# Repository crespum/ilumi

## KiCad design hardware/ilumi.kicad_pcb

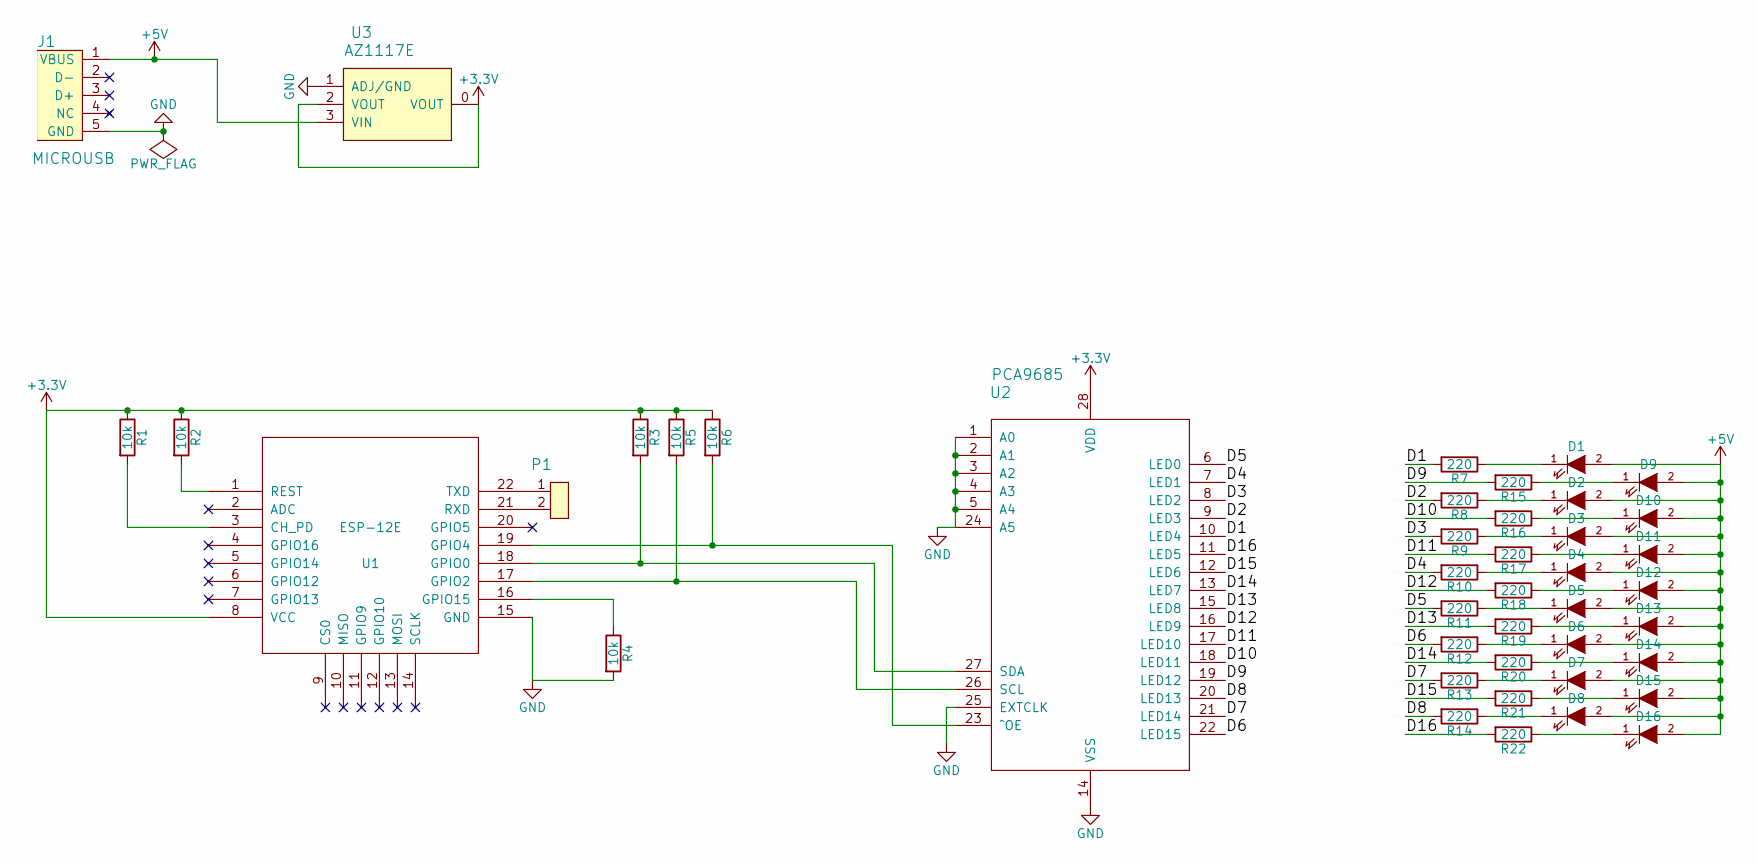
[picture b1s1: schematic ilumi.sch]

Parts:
D1, D2, D3, D4, D5, D6, D7, D8, D9, D10, D11, D12, D13, D14, D15, D16: LED; LED_ILUMI
J1: MICROUSB; MICROUSB_th
P1: 2PIN_MALE; SIP2
R1, R2, R3, R4, R5, R6: 10k; R_0603
R7, R8, R9, R10, R11, R12, R13, R14, R15, R16, R17, R18, R19, R20, R21, R22: 220; R_0603
U1: ESP-12E
U2: PCA9685; HTSSOP28
U3: AZ1117E; SOT223

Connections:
+3V3: R1.1, R2.1, R3.1, R5.1, R6.1, U1.8 (VCC), U2.28 (VDD), U3.0 (VOUT), U3.2 (VOUT)
+5V: D1.2 (A), D2.2 (A), D3.2 (A), D4.2 (A), D5.2 (A), D6.2 (A), D7.2 (A), D8.2 (A), D9.2 (A), D10.2 (A), D11.2 (A), D12.2 (A), D13.2 (A), D14.2 (A), D15.2 (A), D16.2 (A), J1.1 (VBUS), U3.3 (VIN)
/D1: R7.2, U2.10 (LED4)
/D2: R8.2, U2.9 (LED3)
/D3: R9.2, U2.8 (LED2)
/D4: R10.2, U2.7 (LED1)
/D5: R11.2, U2.6 (LED0)
/D6: R12.2, U2.22 (LED15)
/D7: R13.2, U2.21 (LED14)
/D8: R14.2, U2.20 (LED13)
/D9: R15.2, U2.19 (LED12)
/D10: R16.2, U2.18 (LED11)
/D11: R17.2, U2.17 (LED10)
/D12: R18.2, U2.16 (LED9)
/D13: R19.2, U2.15 (LED8)
/D14: R20.2, U2.13 (LED7)
/D15: R21.2, U2.12 (LED6)
/D16: R22.2, U2.11 (LED5)
GND: J1.5 (GND), R4.2, U1.15 (GND), U2.1 (A0), U2.2 (A1), U2.3 (A2), U2.4 (A3), U2.5 (A4), U2.14 (VSS), U2.24 (A5), U2.25 (EXTCLK), U3.1 (ADJ/GND)
unnamed: D1.1 (K), R7.1
unnamed: D2.1 (K), R8.1
unnamed: D3.1 (K), R9.1
unnamed: D4.1 (K), R10.1
unnamed: D5.1 (K), R11.1
unnamed: D6.1 (K), R12.1
unnamed: D7.1 (K), R13.1
unnamed: D8.1 (K), R14.1
unnamed: D9.1 (K), R15.1
unnamed: D10.1 (K), R16.1
unnamed: D11.1 (K), R17.1
unnamed: D12.1 (K), R18.1
unnamed: D13.1 (K), R19.1
unnamed: D14.1 (K), R20.1
unnamed: D15.1 (K), R21.1
unnamed: D16.1 (K), R22.1
unnamed: P1.1, U1.22 (TXD)
unnamed: P1.2, U1.21 (RXD)
unnamed: R1.2, U1.3 (CH_PD)
unnamed: R2.2, U1.1 (REST)
unnamed: R3.2, U1.18 (GPIO0), U2.27 (SDA)
unnamed: R4.1, U1.16 (GPIO15)
unnamed: R5.2, U1.17 (GPIO2), U2.26 (SCL)
unnamed: R6.2, U1.19 (GPIO4), U2.23 (^OE)

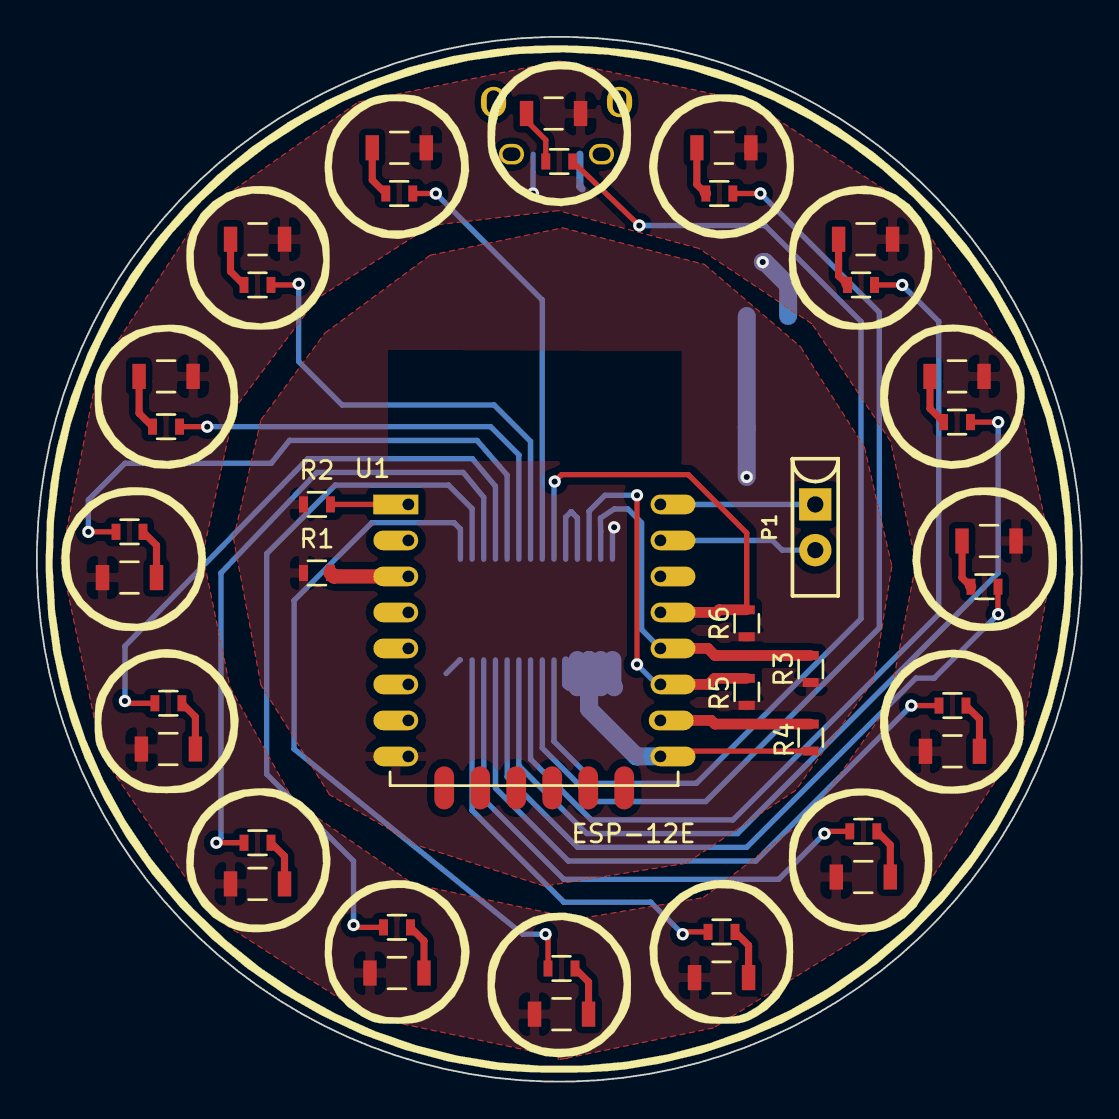
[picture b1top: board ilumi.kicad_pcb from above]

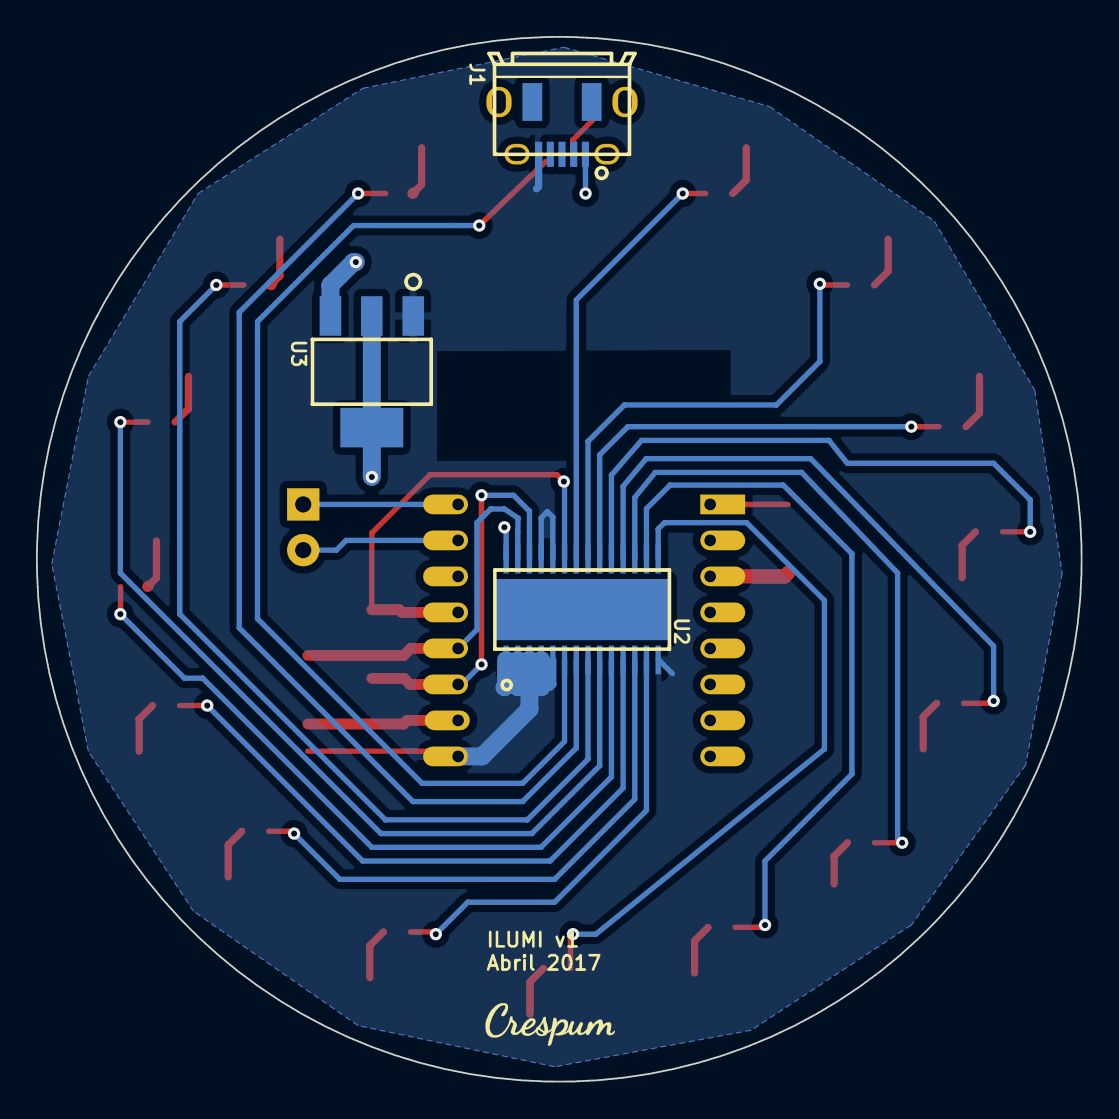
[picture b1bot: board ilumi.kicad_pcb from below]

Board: 2 copper layers, 58.0 x 58.0 mm, 43 parts (3 on the bottom side), 43 nets.

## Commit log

2017-06-07 [HW] PCB v1
2017-07-13 [PCB] Fix v1 issues - Add GND in UART header - Power LEDs driver with 5V
2017-07-13 [PCA9685] Basic driver implementation
2017-07-13 [FW] Basic light effects
2018-02-13 fw: switch to Arduino-based firmware
2018-02-20 fw: switch PCA9685 library
2018-02-20 fw: correct LED on/off function call
2018-02-20 fw: integrate with home assistant
2018-02-20 fw: update brightness status
2018-03-09 Add submodules/libraries
2018-03-09 Fix MQTT topic
